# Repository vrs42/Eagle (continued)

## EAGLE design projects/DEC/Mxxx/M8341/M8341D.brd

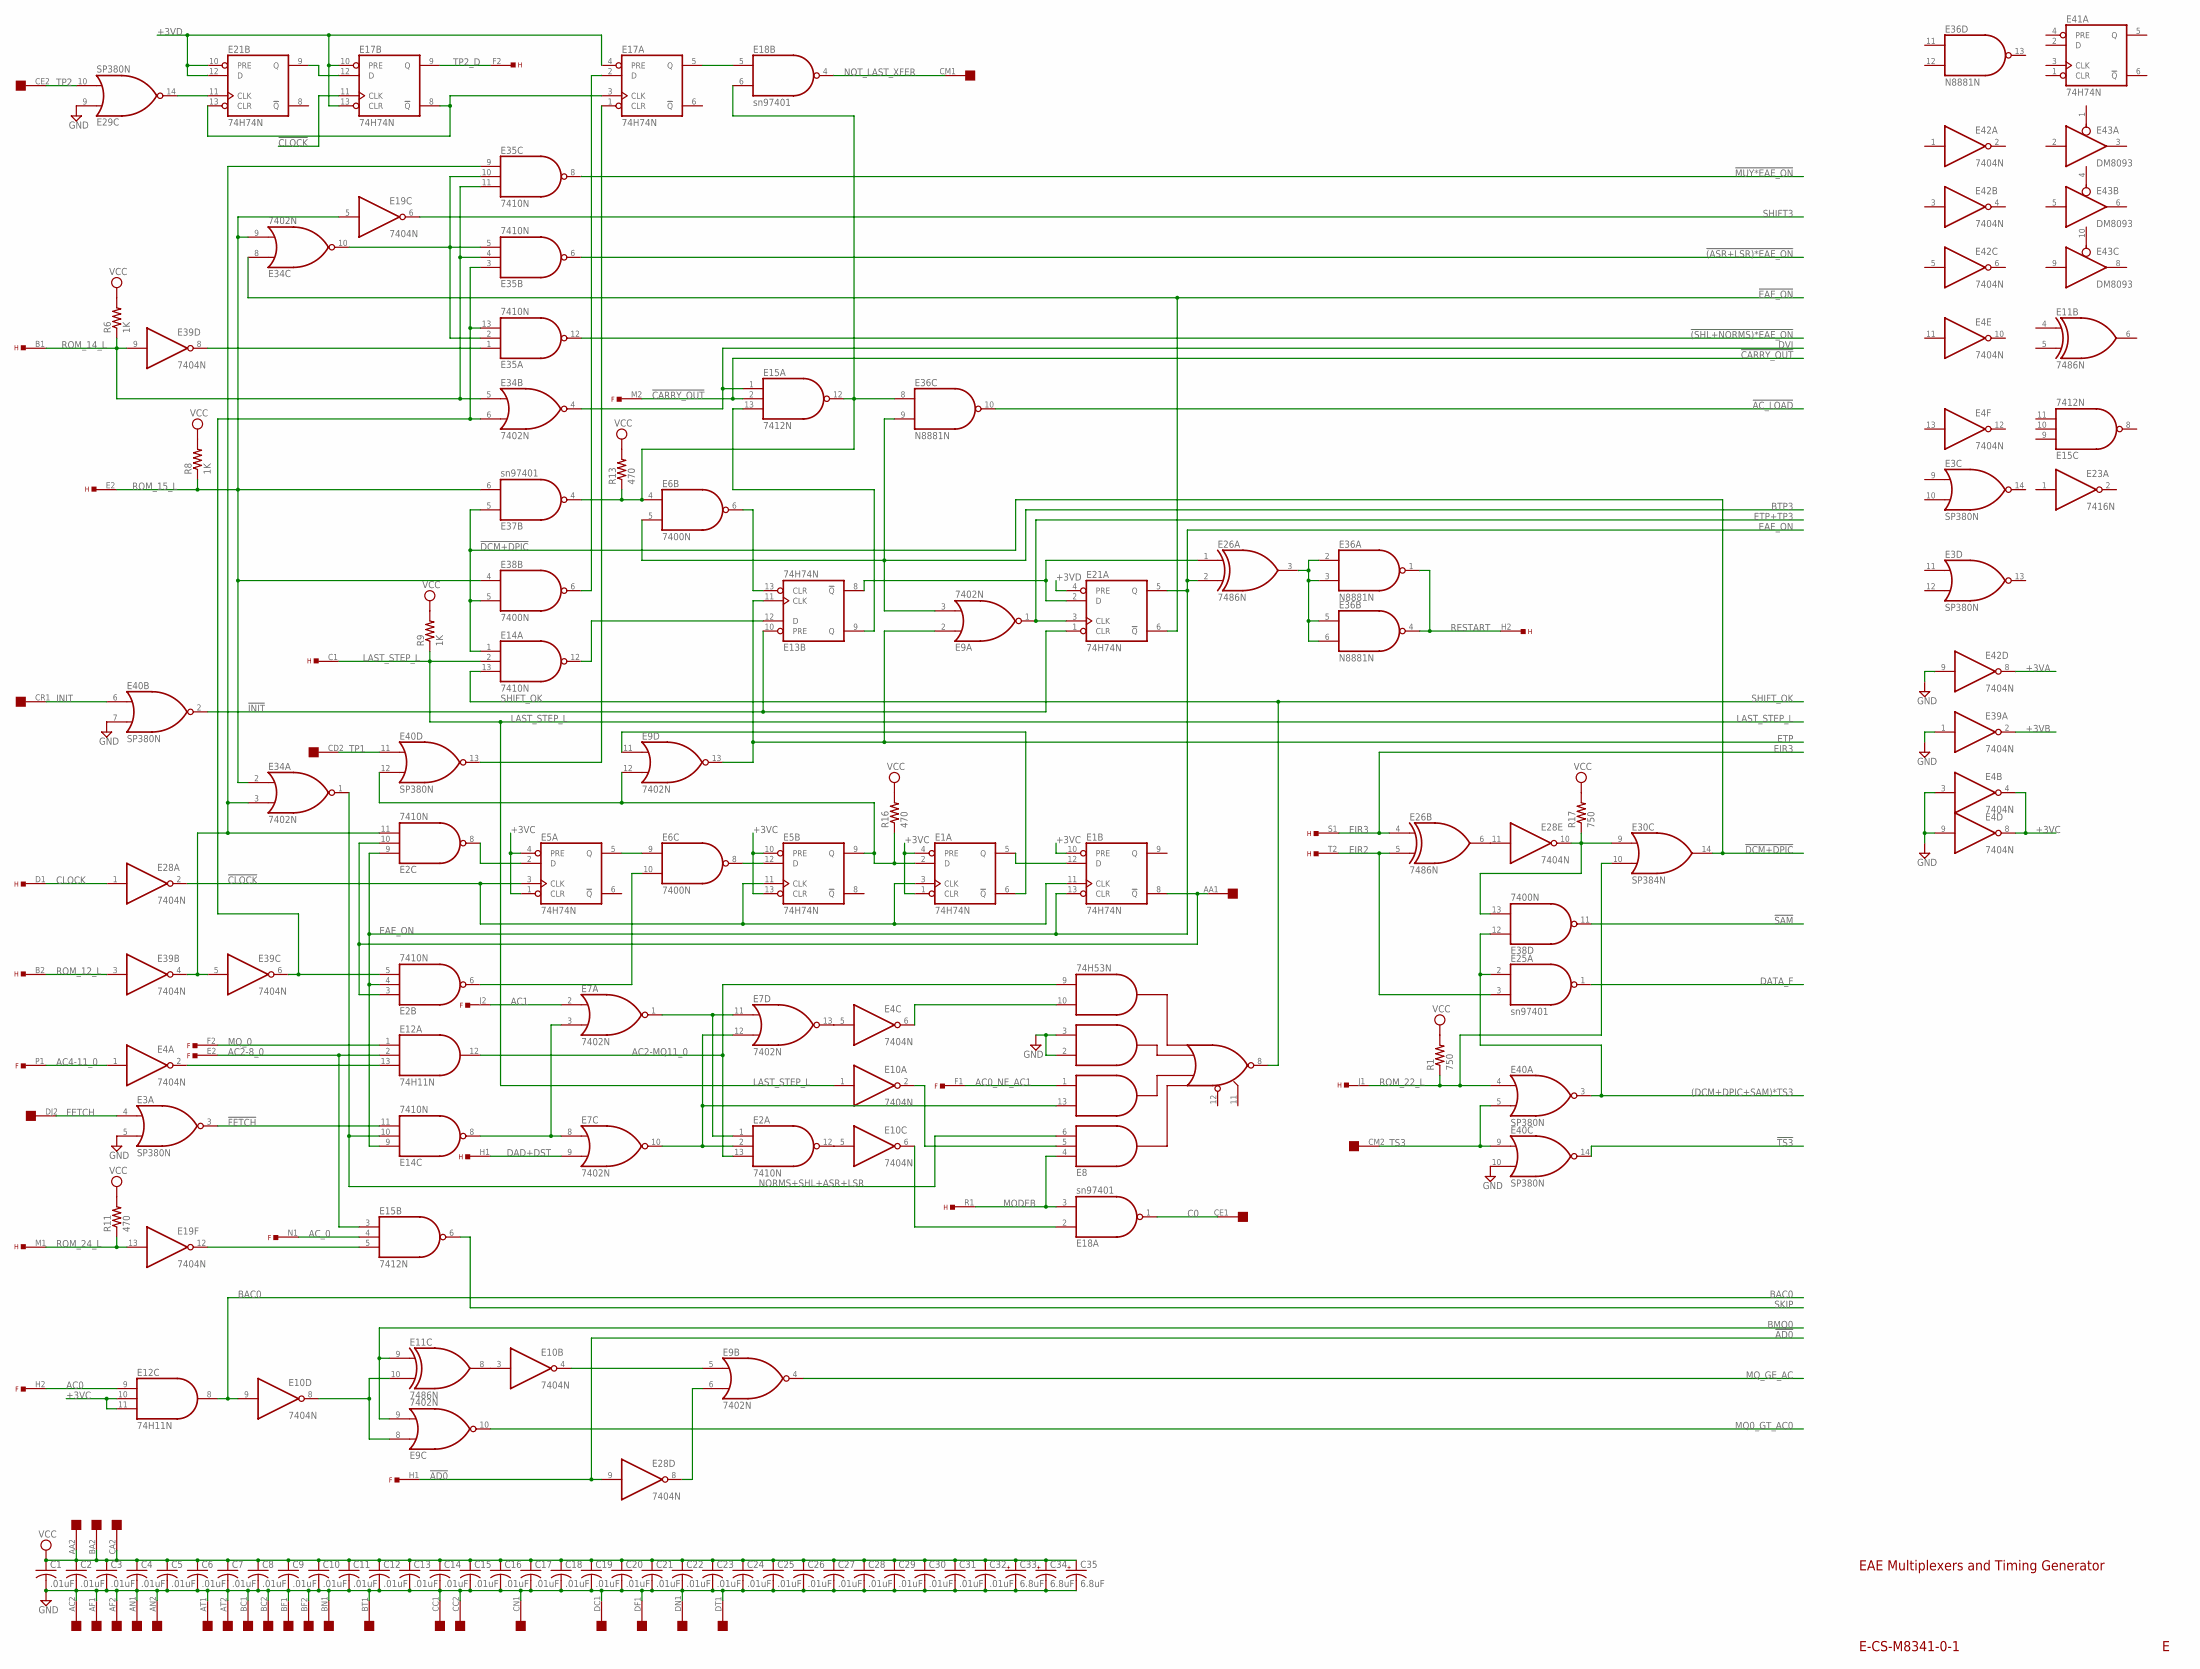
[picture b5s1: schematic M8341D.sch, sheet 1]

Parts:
C1, C2, C3, C4, C5, C6, C7, C8, C9, C10, C11, C12, C13, C14, C15, C16, C17, C18, C19, C20, C21, C22, C23, C24, C25, C26, C27, C28, C29, C30, C31, C32: .01uF; C063-025X075
C33, C34, C35: 6.8uF; E12-8
E1, E5, E13, E17, E21, E41: 74H74N; DIL14
E2, E14, E35: 7410N; DIL14
E3, E29, E40: SP380N; DIL14
E4, E10, E19, E28, E39, E42: 7404N; DIL14
E6, E38: 7400N; DIL14
E7, E9, E34: 7402N; DIL14
E8: 74H53N; DIL14
E11, E26: 7486N; DIL14
E12: 74H11N; DIL14
E15: 7412N; DIL14
E18, E25, E37: sn97401; DIL14
E23: 7416N; DIL14
E30: SP384N; DIL14
E36: N8881N; DIL14
E43: DM8093; DIL14
F: EDGE-TOP; EDGE-CON2
H: EDGE-TOP; EDGE-CON2
R1, R17: 750; 0207/10
R6, R8, R9: 1K; 0207/10
R11, R13, R16: 470; 0207/10
U$2: QUAD; EDGE-CON8

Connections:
!(ASR+LSR)*EAE_ON: E35.6 (O); also elsewhere on the board
!(SHL+NORMS)*EAE_ON: E35.12 (O); also elsewhere on the board
!AC_LOAD: E36.10 (O); also elsewhere on the board
!AD0: E28.9 (I), F.H1; also elsewhere on the board
!CARRY_OUT: E15.2 (I1), F.M2; also elsewhere on the board
!CLOCK: E1.3 (CLK), E1.11 (CLK), E5.3 (CLK), E5.11 (CLK), E17.11 (CLK), E28.2 (O)
!DCM+DPIC: E14.1 (I0), E30.14 (O), E37.5 (I0), E38.5 (I1); also elsewhere on the board
!EAE_ON: E21.6 (!Q), E34.8 (I0); also elsewhere on the board
!FETCH: E3.3 (O), E14.11 (I2)
!INIT: E13.10 (PRE), E21.1 (CLR), E40.2 (O)
!MUY*EAE_ON: E35.8 (O); also elsewhere on the board
!SAM: E38.11 (O); also elsewhere on the board
!TS3: E40.14 (O); also elsewhere on the board
(DCM+DPIC+SAM)*TS3: E25.2 (I0), E38.12 (I0), E40.3 (O); also elsewhere on the board
+3VA: E42.8 (O); also elsewhere on the board
+3VB: E39.2 (O); also elsewhere on the board
+3VC: E1.1 (CLR), E1.4 (PRE), E1.10 (PRE), E4.4 (O), E4.8 (O), E5.1 (CLR), E5.4 (PRE), E5.10 (PRE), E5.13 (CLR), E12.10 (I1), E12.11 (I2); also elsewhere on the board
+3VD: E17.4 (PRE), E17.10 (PRE), E17.13 (CLR), E21.4 (PRE), E21.10 (PRE), E21.12 (D); also elsewhere on the board
AC0: E12.9 (I0), F.H2
AC0_NE_AC1: E8.1 (I4), F.F1
AC1: E7.2 (I0), F.J2
AC2-8_0: E12.2 (I1), E15.3 (I0), F.E2
AC2-MQ11_0: E2.13 (I2), E8.9 (I8), E12.12 (O)
AC4-11_0: E4.1 (I), F.P1
AC_0: E15.4 (I1), F.N1
BAC0: E10.9 (I), E12.8 (O); also elsewhere on the board
BMQ0: E9.9 (I1), E11.9 (I0); also elsewhere on the board
BTP3: E6.5 (I1), E9.3 (I1), E36.9 (I1); also elsewhere on the board
C0: E18.1 (O), U$2.CE1
CLOCK: E28.1 (I), H.D1
DAD+DST: E7.9 (I1), H.H1
DATA_F: E25.1 (O); also elsewhere on the board
DVI: E15.1 (I0), E34.4 (O); also elsewhere on the board
EAE_ON: E1.13 (CLR), E2.4 (I1), E2.9 (I0), E14.9 (I0), E21.5 (Q), E26.2 (I1); also elsewhere on the board
EIR2: E25.3 (I1), E26.5 (I1), H.T2
EIR3: E26.4 (I0), H.S1; also elsewhere on the board
ETP: E9.2 (I0), E9.13 (O), E13.11 (CLK); also elsewhere on the board
ETP+TP3: E9.1 (O), E21.3 (CLK); also elsewhere on the board
FETCH: E3.4 (I0), U$2.DJ2
GND: C1.2, C2.2, C3.2, C4.2, C5.2, C6.2, C7.2, C8.2, C9.2, C10.2, C11.2, C12.2, C13.2, C14.2, C15.2, C16.2, C17.2, C18.2, C19.2, C20.2, C21.2, C22.2, C23.2, C24.2, C25.2, C26.2, C27.2, C28.2, C29.2, C30.2, C31.2, C32.2, C33.-, C34.-, C35.-, E1.7 (GND), E2.7 (GND), E3.1 (GND), E3.5 (I1), E4.3 (I), E4.7 (GND), E4.9 (I), E5.7 (GND), E6.7 (GND), E7.7 (GND), E8.2 (I5), E8.3 (I6), E8.7 (GND), E9.7 (GND), E10.7 (GND), E11.7 (GND), E12.7 (GND), E13.7 (GND), E14.7 (GND), E15.7 (GND), E17.7 (GND), E18.7 (GND), E19.7 (GND), E21.7 (GND), E23.7 (GND), E25.7 (GND), E26.7 (GND), E28.7 (GND), E29.1 (GND), E29.9 (I0), E30.1 (GND), E34.7 (GND), E35.7 (GND), E36.7 (GND), E37.7 (GND), E38.7 (GND), E39.1 (I), E39.7 (GND), E40.1 (GND), E40.7 (I1), E40.10 (I1), E41.7 (GND), E42.7 (GND), E42.9 (I), E43.7 (GND), U$2.AC2, U$2.AF1, U$2.AF2, U$2.AN1, U$2.AN2, U$2.AT1, U$2.AT2, U$2.BC1, U$2.BC2, U$2.BF1, U$2.BF2, U$2.BN1, U$2.BT1, U$2.CC1, U$2.CC2, U$2.CN1, U$2.DC1, U$2.DF1, U$2.DN1, U$2.DT1; also elsewhere on the board
INIT: E40.6 (I0), U$2.CR1
LAST_STEP_L: E10.1 (I), E14.2 (I1), H.C1, R9.1; also elsewhere on the board
MODEB: E8.4 (I1), E18.3 (I1), H.R1; also elsewhere on the board
MQ0_GT_AC0: E9.10 (O); also elsewhere on the board
MQ_0: E12.1 (I0), F.F2
MQ_GE_AC: E9.4 (O); also elsewhere on the board
unnamed: E21.11 (CLK), E29.14 (O)
unnamed: E26.3 (O), E36.2 (I0), E36.3 (I1), E36.5 (I0), E36.6 (I1)
unnamed: E6.4 (I0), E15.12 (O), E18.6 (I1), E36.8 (I0), E37.4 (O), R13.1
unnamed: E4.2 (O), E12.13 (I2)
unnamed: E13.8 (!Q), E21.2 (D), E26.1 (I0)
unnamed: E2.5 (I2), E34.6 (I1), E35.3 (I0), E35.13 (I2), E39.6 (O)
unnamed: E9.8 (I0), E10.8 (O), E11.10 (I1)
unnamed: E15.5 (I2), E19.12 (O)
unnamed: E7.3 (I1), E7.8 (I0), E14.8 (O)
unnamed: E9.6 (I1), E28.8 (O)
unnamed: E9.5 (I0), E10.4 (O)
unnamed: E2.2 (I1), E7.10 (O), E7.12 (I1), E8.13 (I3)
unnamed: E2.12 (O), E10.5 (I)
unnamed: E10.6 (O), E18.2 (I0)
unnamed: E5.12 (D), E6.8 (O)
unnamed: E1.2 (D), E5.9 (Q), E9.12 (I1), E40.12 (I1), R16.1
unnamed: E1.5 (Q), E1.12 (D)
unnamed: E26.6 (O), E28.11 (I)
unnamed: E2.1 (I0), E7.1 (O), E7.11 (I0)
unnamed: E4.5 (I), E7.13 (O)
unnamed: E4.6 (O), E8.10 (I7)
unnamed: E8.5 (I11), E10.2 (O)
unnamed: E28.10 (O), E30.9 (I0), E38.13 (I1), R17.1
unnamed: E35.1 (I0), E39.8 (O)
unnamed: E17.3 (CLK), E17.8 (!Q), E21.13 (CLR)
unnamed: E17.12 (D), E21.9 (Q)
unnamed: E34.10 (O), E35.2 (I1), E35.5 (I2), E35.10 (I1)
unnamed: E1.6 (!Q), E9.11 (I0)
unnamed: E2.8 (O), E5.2 (D)
unnamed: E5.5 (Q), E6.9 (I0)
unnamed: E17.2 (D), E38.6 (O)
unnamed: E17.1 (CLR), E40.13 (O)
unnamed: E17.5 (Q), E18.5 (I0)
unnamed: E6.6 (O), E13.13 (CLR)
unnamed: E13.12 (D), E14.12 (O)
unnamed: E2.6 (O), E6.10 (I1)
unnamed: E10.3 (I), E11.8 (O)
unnamed: E13.9 (Q), E15.13 (I2)
NORMS+SHL+ASR+LSR: E8.6 (I2), E14.10 (I1), E34.1 (O)
NOT_LAST_XFER: E18.4 (O), U$2.CM1
RESTART: E36.1 (O), E36.4 (O), H.H2
ROM_12: E2.11 (I2), E34.3 (I1), E35.9 (I0), E39.4 (O), E39.5 (I)
ROM_12_L: E39.3 (I), H.B2
ROM_14_L: E34.5 (I0), E35.4 (I1), E35.11 (I2), E39.9 (I), H.B1, R6.1
ROM_15_L: E19.5 (I), E34.2 (I0), E34.9 (I1), E37.6 (I1), E38.4 (I0), H.E2, R8.1
ROM_22_L: E30.10 (I1), E40.4 (I0), H.J1, R1.1
ROM_24_L: E19.13 (I), H.M1, R11.1
SHIFT3: E19.6 (O); also elsewhere on the board
SHIFT_OK: E8.8 (O), E14.13 (I2); also elsewhere on the board
SKIP: E15.6 (O); also elsewhere on the board
TP: E1.8 (!Q), E2.3 (I0), E2.10 (I1), U$2.AA1
TP1: E40.11 (I0), U$2.CD2
TP2: E29.10 (I1), U$2.CE2
TP2_D: E17.9 (Q), H.F2
TS3: E40.5 (I1), E40.9 (I0), U$2.CM2
VCC: C1.1, C2.1, C3.1, C4.1, C5.1, C6.1, C7.1, C8.1, C9.1, C10.1, C11.1, C12.1, C13.1, C14.1, C15.1, C16.1, C17.1, C18.1, C19.1, C20.1, C21.1, C22.1, C23.1, C24.1, C25.1, C26.1, C27.1, C28.1, C29.1, C30.1, C31.1, C32.1, C33.+, C34.+, C35.+, E1.14 (VCC), E2.14 (VCC), E3.8 (VCC), E4.14 (VCC), E5.14 (VCC), E6.14 (VCC), E7.14 (VCC), E8.14 (VCC), E9.14 (VCC), E10.14 (VCC), E11.14 (VCC), E12.14 (VCC), E13.14 (VCC), E14.14 (VCC), E15.14 (VCC), E17.14 (VCC), E18.14 (VCC), E19.14 (VCC), E21.14 (VCC), E23.14 (VCC), E25.14 (VCC), E26.14 (VCC), E28.14 (VCC), E29.8 (VCC), E30.8 (VCC), E34.14 (VCC), E35.14 (VCC), E36.14 (VCC), E37.14 (VCC), E38.14 (VCC), E39.14 (VCC), E40.8 (VCC), E41.14 (VCC), E42.14 (VCC), E43.14 (VCC), R1.2, R6.2, R8.2, R9.2, R11.2, R13.2, R16.2, R17.2, U$2.AA2, U$2.BA2, U$2.CA2; also elsewhere on the board

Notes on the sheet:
E-CS-M8341-0-1
EAE Multiplexers and Timing Generator

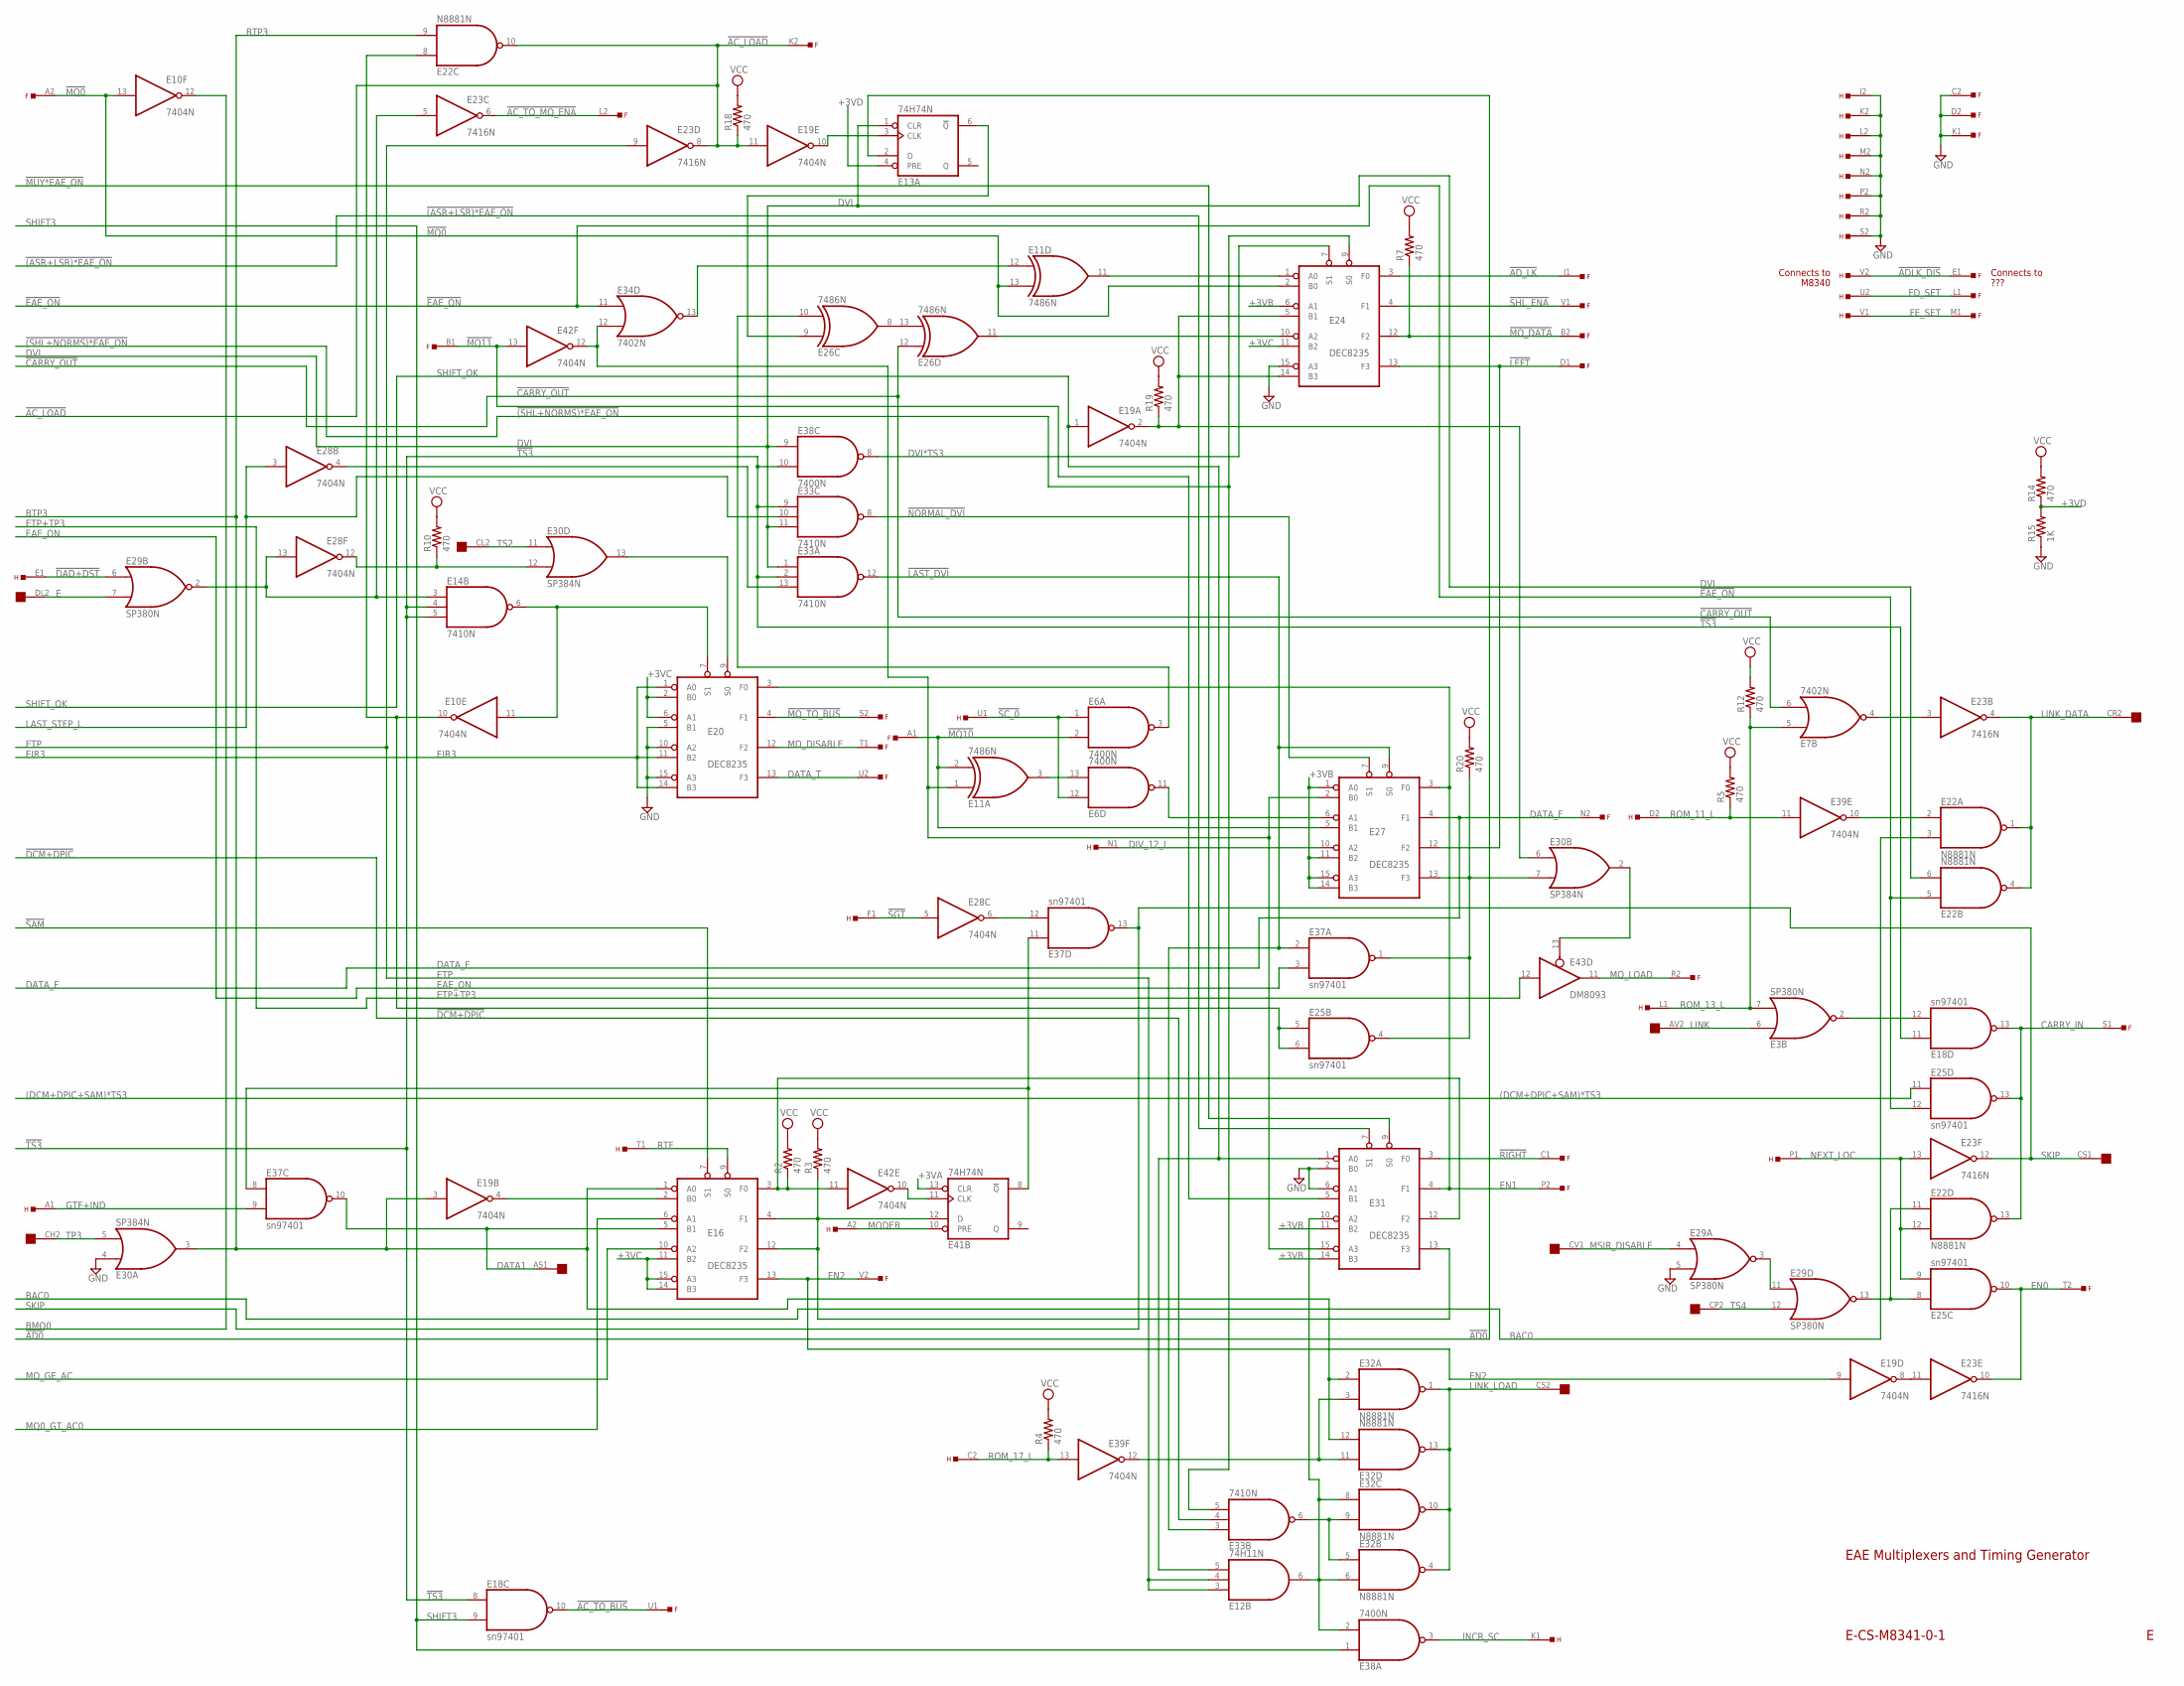
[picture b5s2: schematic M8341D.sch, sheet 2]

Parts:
E3, E29: SP380N; DIL14
E6, E38: 7400N; DIL14
E7, E34: 7402N; DIL14
E10, E19, E28, E39, E42: 7404N; DIL14
E11, E26: 7486N; DIL14
E12: 74H11N; DIL14
E13, E41: 74H74N; DIL14
E14, E33: 7410N; DIL14
E16, E20, E24, E27, E31: DEC8235; DIL16
E18, E25, E37: sn97401; DIL14
E22, E32: N8881N; DIL14
E23: 7416N; DIL14
E30: SP384N; DIL14
E43: DM8093; DIL14
F: EDGE-TOP; EDGE-CON2
H: EDGE-TOP; EDGE-CON2
R2, R3, R4, R5, R7, R10, R12, R14, R18, R19, R20: 470; 0207/10
R15: 1K; 0207/10
U$2: QUAD; EDGE-CON8

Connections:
!(ASR+LSR)*EAE_ON: E31.7 (S1); also elsewhere on the board
!(SHL+NORMS)*EAE_ON: E24.9 (S0), E33.5 (I2); also elsewhere on the board
!AC_LOAD: E19.11 (I), E22.10 (O), E23.8 (O), F.K2, R18.1; also elsewhere on the board
!AC_TO_BUS: E18.10 (O), F.U1
!AC_TO_MQ_ENA: E23.6 (O), F.L2
!AD0: E13.2 (D); also elsewhere on the board
!ADLK_DIS: F.E1, H.V2
!AD_LK: E24.3 (F0), F.J1
!CARRY_OUT: E7.6 (I1), E26.12 (I0); also elsewhere on the board
!DAD+DST: E29.6 (I0), H.E1
!DCM+DPIC: E33.4 (I1); also elsewhere on the board
!EAE_ON: E22.5 (I0), E25.12 (I1), E34.11 (I0); also elsewhere on the board
!LAST_DVI: E27.9 (S0), E33.3 (I0), E33.12 (O), E37.2 (I0)
!LEFT: E24.13 (F3), E27.12 (F2), F.D1
!MQ0: E10.13 (I), E11.13 (I1), E24.2 (B0), F.A2
!MQ10: E6.2 (I1), E11.2 (I1), E27.5 (B1), F.A1
!MQ11: E31.5 (B1), E42.13 (I), F.B1
!MQ_DATA: E24.12 (F2), F.B2, R7.1
!MQ_TO_BUS: E20.4 (F1), F.S2
!MUY*EAE_ON: E31.9 (S0); also elsewhere on the board
!NORMAL_DVI: E27.7 (S1), E33.8 (O)
!RIGHT: E31.3 (F0), F.C1
!SAM: E16.7 (S1); also elsewhere on the board
!SC_0: E6.1 (I0), E6.12 (I0), H.U1
!SGT: E28.5 (I), H.F1
!SHL_ENA: E24.4 (F1), F.V1
!TS3: E14.4 (I1), E14.5 (I2), E18.8 (I0), E18.11 (I0), E33.2 (I1), E33.9 (I0), E38.10 (I1); also elsewhere on the board
(DCM+DPIC+SAM)*TS3: E25.11 (I0); also elsewhere on the board
+3VA: E41.13 (CLR); also elsewhere on the board
+3VB: E24.6 (A1), E27.1 (A0), E27.11 (B2), E27.14 (B3), E27.15 (A3), E31.11 (B2), E31.14 (B3); also elsewhere on the board
+3VC: E16.11 (B2), E16.14 (B3), E16.15 (A3), E20.2 (B0), E20.6 (A1), E24.11 (B2); also elsewhere on the board
+3VD: E13.4 (PRE), R14.1, R15.2; also elsewhere on the board
BAC0: E22.3 (I1); also elsewhere on the board
BMQ0: E10.12 (O); also elsewhere on the board
BTP3: E16.1 (A0), E19.3 (I), E22.9 (I1), E30.3 (O), E32.2 (I0), E32.12 (I1); also elsewhere on the board
CARRY_IN: E18.13 (O), E22.13 (O), E25.13 (O), F.S1
DATA1: E16.5 (B1), E37.10 (O), U$2.AS1
DATA_F: E27.4 (F1), F.N2; also elsewhere on the board
DATA_T: E20.13 (F3), F.U2
DIV_12_L: E27.10 (A2), H.N1
DVI: E13.1 (CLR), E22.6 (I1), E33.1 (I0), E33.11 (I2), E38.9 (I0); also elsewhere on the board
DVI*TS3: E24.7 (S1), E38.8 (O)
E: E29.7 (I1), U$2.DL2
EAE_ON: E37.3 (I1); also elsewhere on the board
EIR3: E20.1 (A0), E20.11 (B2), E20.14 (B3); also elsewhere on the board
EN0: E23.10 (O), E25.10 (O), F.T2
EN1: E20.3 (F0), E27.3 (F0), E31.4 (F1), F.P2
EN2: E16.13 (F3), E19.9 (I), F.V2
ETP: E12.3 (I0), E12.4 (I1), E23.9 (I); also elsewhere on the board
ETP+TP3: E43.12 (I); also elsewhere on the board
FD_SET: F.L1, H.U2
FE_SET: F.M1, H.V1
GND: E3.1 (GND), E6.7 (GND), E7.7 (GND), E10.7 (GND), E11.7 (GND), E12.7 (GND), E13.7 (GND), E14.7 (GND), E16.8 (GND), E18.7 (GND), E19.7 (GND), E20.5 (B1), E20.8 (GND), E20.10 (A2), E20.15 (A3), E22.7 (GND), E23.7 (GND), E24.8 (GND), E24.15 (A3), E25.7 (GND), E26.7 (GND), E27.8 (GND), E28.7 (GND), E29.1 (GND), E29.5 (I1), E30.1 (GND), E30.4 (I0), E31.2 (B0), E31.6 (A1), E31.8 (GND), E32.7 (GND), E33.7 (GND), E34.7 (GND), E37.7 (GND), E38.7 (GND), E39.7 (GND), E41.7 (GND), E42.7 (GND), E43.7 (GND), F.C2, F.D2, F.K1, H.J2, H.K2, H.L2, H.M2, H.N2, H.P2, H.R2, H.S2, R15.1; also elsewhere on the board
GTF+IND: E37.9 (I1), H.A1
INCR_SC: E38.3 (O), H.K1
LAST_STEP_L: E28.3 (I), E33.10 (I1); also elsewhere on the board
LINK: E3.6 (I0), U$2.AV2
LINK_DATA: E22.1 (O), E22.4 (O), E23.4 (O), U$2.CR2
LINK_LOAD: E32.1 (O), E32.4 (O), E32.10 (O), E32.13 (O), U$2.CS2
MD_DISABLE: E20.12 (F2), F.T1
MODEB: E41.10 (PRE), H.A2; also elsewhere on the board
MQ0_GT_AC0: E16.6 (A1); also elsewhere on the board
MQ_GE_AC: E16.10 (A2); also elsewhere on the board
MQ_LOAD: E43.11 (O), F.R2
MSIR_DISABLE: E29.4 (I0), U$2.CV1
unnamed: E11.1 (I0), E27.2 (B0), E31.15 (A3), E34.12 (I1), E42.12 (O)
unnamed: E20.9 (S0), E30.13 (O)
unnamed: E10.10 (O), E22.8 (I0), E25.5 (I0), E25.6 (I1)
unnamed: E37.8 (I0), E37.11 (I0), E41.8 (!Q)
unnamed: E16.2 (B0), E19.4 (O)
unnamed: E14.3 (I0), E23.5 (I), E28.13 (I), E29.2 (O)
unnamed: E28.12 (O), E30.12 (I1), R10.1
unnamed: E10.11 (I), E14.6 (O), E20.7 (S1)
unnamed: E11.11 (O), E24.1 (A0)
unnamed: E13.3 (CLK), E19.10 (O)
unnamed: E6.3 (O), E26.10 (I1)
unnamed: E28.6 (O), E37.12 (I1)
unnamed: E16.4 (F1), E16.12 (F2), E31.13 (F3), E41.12 (D), R3.1
unnamed: E41.11 (CLK), E42.10 (O)
unnamed: E13.6 (!Q), E26.9 (I0)
unnamed: E16.3 (F0), E31.12 (F2), E42.11 (I), R2.1
unnamed: E32.5 (I0), E32.9 (I1), E33.6 (O)
unnamed: E25.4 (O), E27.13 (F3), E30.7 (I1), E37.1 (O), R20.1
unnamed: E19.2 (O), E24.5 (B1), E24.14 (B3), E30.6 (I0), R19.1
unnamed: E7.4 (O), E23.3 (I)
unnamed: E22.2 (I0), E39.10 (O)
unnamed: E30.2 (O), E43.13 (OE)
unnamed: E3.2 (O), E18.12 (I1)
unnamed: E29.3 (O), E29.11 (I0)
unnamed: E22.11 (I0), E25.8 (I0), E29.13 (O)
unnamed: E19.8 (O), E23.11 (I)
unnamed: E12.6 (O), E31.10 (A2), E32.6 (I1), E32.8 (I0), E38.2 (I1)
unnamed: E24.10 (A2), E26.11 (O)
unnamed: E11.12 (I0), E34.13 (O)
unnamed: E32.3 (I1), E32.11 (I0), E39.12 (O)
unnamed: E6.11 (O), E27.6 (A1)
unnamed: E6.13 (I1), E11.3 (O)
unnamed: E28.4 (O), E33.13 (I2)
unnamed: E26.8 (O), E26.13 (I1)
NEXT_LOC: E22.12 (I1), E23.13 (I), E25.9 (I1), H.P1
ROM_11_L: E39.11 (I), H.D2, R5.1
ROM_13_L: E3.7 (I1), E7.5 (I0), H.L1, R12.1
ROM_17_L: E39.13 (I), H.C2, R4.1
RTF: E16.9 (S0), H.T1
SHIFT3: E18.9 (I1), E38.1 (I0); also elsewhere on the board
SHIFT_OK: E12.5 (I2), E19.1 (I), E31.1 (A0); also elsewhere on the board
SKIP: E23.12 (O), E37.13 (O), U$2.CS1; also elsewhere on the board
TP3: E30.5 (I1), U$2.CH2
TS2: E30.11 (I0), U$2.CL2
TS4: E29.12 (I1), U$2.CP2
VCC: E3.8 (VCC), E6.14 (VCC), E7.14 (VCC), E10.14 (VCC), E11.14 (VCC), E12.14 (VCC), E13.14 (VCC), E14.14 (VCC), E16.16 (VCC), E18.14 (VCC), E19.14 (VCC), E20.16 (VCC), E22.14 (VCC), E23.14 (VCC), E24.16 (VCC), E25.14 (VCC), E26.14 (VCC), E27.16 (VCC), E28.14 (VCC), E29.8 (VCC), E30.8 (VCC), E31.16 (VCC), E32.14 (VCC), E33.14 (VCC), E34.14 (VCC), E37.14 (VCC), E38.14 (VCC), E39.14 (VCC), E41.14 (VCC), E42.14 (VCC), E43.14 (VCC), R2.2, R3.2, R4.2, R5.2, R7.2, R10.2, R12.2, R14.2, R18.2, R19.2, R20.2; also elsewhere on the board

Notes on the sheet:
???
Connects to
M8340
E-CS-M8341-0-1
EAE Multiplexers and Timing Generator

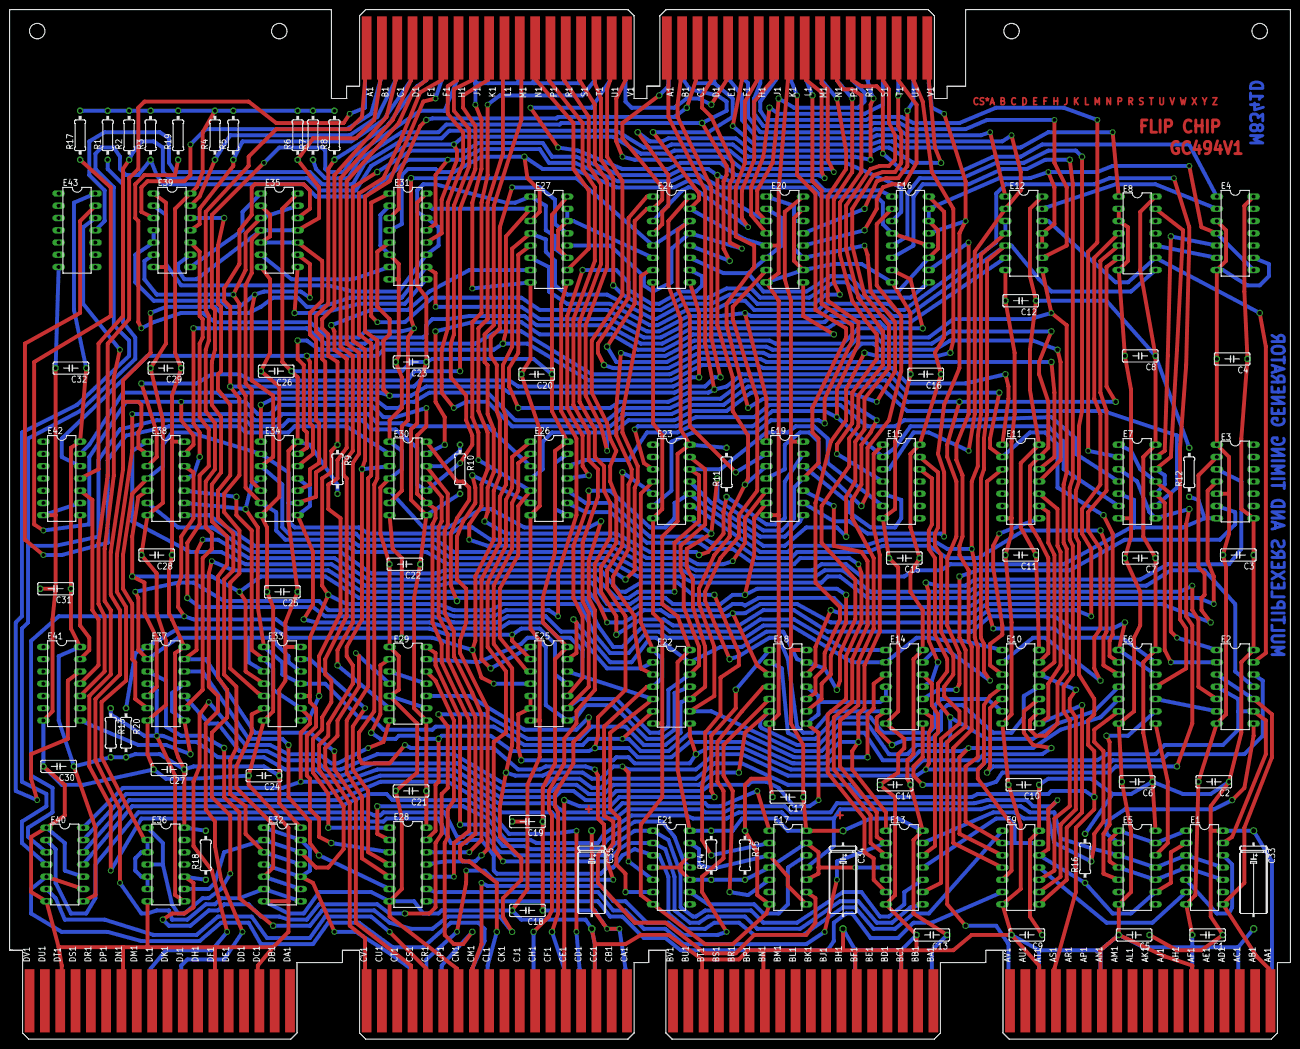
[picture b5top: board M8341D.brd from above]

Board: 3 copper layers, 265.4 x 213.4 mm, 101 parts (0 on the bottom side), 180 nets.
